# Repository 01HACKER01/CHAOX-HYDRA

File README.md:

# CHAOX-HYDRA

## What is this 
this is a diy flipper 0 which i tried to make it has 7 buttons and a screen it works on a esp32 mini.

## why it exists
i was quite amazed by the flipper 0 like how it can change the traffic lights and steal any rfid connections so i was amazed by its powers so i thought lets try to make this i thought i will watch like how it works but studying is quite boring.

## how to assemble
the pcb is connected to the case using glue or double sided tape adn teh case is connected together using brass inserts adn screws.

## Issues 
i dont think it has some issues but if u think it has some issues please let me know ill try to fix them right away.

## BOM

| Component | Qty | Est. Unit Price | Estimated Total | Purchase Link |
|---|---:|---:|---:|---|
| Seeed XIAO ESP32-C5 | 1 | $7–12 | $7–12 | [Alibaba](https://www.alibaba.com/trade/search?SearchText=Seeed+XIAO+ESP32-C5) |
| MCP23017 I/O Expander | 1 | $1–3 | $1–3 | [Alibaba](https://www.alibaba.com/trade/search?SearchText=MCP23017+module) |
| LIS3DH Accelerometer | 1 | $2–5 | $2–5 | [Alibaba](https://www.alibaba.com/trade/search?SearchText=LIS3DH+accelerometer+module) |
| SPI TFT Display | 1 | $4–10 | $4–10 | [Alibaba](https://www.alibaba.com/trade/search?SearchText=2.4+inch+SPI+TFT+240x320) |
| MicroSD Socket / Module | 1 | $1–3 | $1–3 | [Alibaba](https://www.alibaba.com/trade/search?SearchText=microSD+SPI+module) |
| CC1101 RF Module | 1 | $2–5 | $2–5 | [Alibaba](https://www.alibaba.com/trade/search?SearchText=CC1101+wireless+module) |
| PN532 NFC Module | 1 | $2–5 | $2–5 | [Alibaba](https://www.alibaba.com/trade/search?SearchText=PN532+NFC+module) |
| IR Receiver | 1 | $0.20–1 | $0.20–1 | [Alibaba](https://www.alibaba.com/trade/search?SearchText=infrared+receiver+38kHz) |
| IR Transmitter LED | 1 | $0.10–0.50 | $0.10–0.50 | [Alibaba](https://www.alibaba.com/trade/search?SearchText=infrared+transmitter+LED) |
| Buzzer | 1 | $0.20–1 | $0.20–1 | [Alibaba](https://www.alibaba.com/trade/search?SearchText=3.3V+active+buzzer) |
| Tactile Buttons | 7 | $0.05–0.20 | $0.35–1.40 | [Alibaba](https://www.alibaba.com/trade/search?SearchText=tactile+push+button+switch) |
| Status LED | 1 | $0.05–0.20 | $0.05–0.20 | [Alibaba](https://www.alibaba.com/trade/search?SearchText=0603+LED) |
| Rechargeable Battery | 1 | $3–7 | $3–7 | [Alibaba](https://www.alibaba.com/trade/search?SearchText=3.7V+rechargeable+LiPo+battery) |
| Battery Charger | 1 | $1–3 | $1–3 | [Alibaba](https://www.alibaba.com/trade/search?SearchText=LiPo+battery+charger+module) |
| Voltage Regulator | 1 | $0.50–2 | $0.50–2 | [Alibaba](https://www.alibaba.com/trade/search?SearchText=voltage+regulator+module) |
| Power Switch | 1 | $0.20–1 | $0.20–1 | [Alibaba](https://www.alibaba.com/trade/search?SearchText=miniature+maintained+power+switch) |
| Passive Components & Connectors | 1 lot | $2–5 | $2–5 | [Alibaba](https://www.alibaba.com/trade/search?SearchText=SMD+resistor+capacitor+connector+kit) |
| Custom PCB | 1 | $10 | $10 | |
| Enclosure & Mounting Hardware | 1 set | $10 | $10 ||

| Category | Estimated Cost |
|---|---:|
| Electronics and modules | $24–60 |
| PCB and enclosure | $8–25 |
| **Estimated overall total** | **$32–100** |

## The END
that was it thank you very much

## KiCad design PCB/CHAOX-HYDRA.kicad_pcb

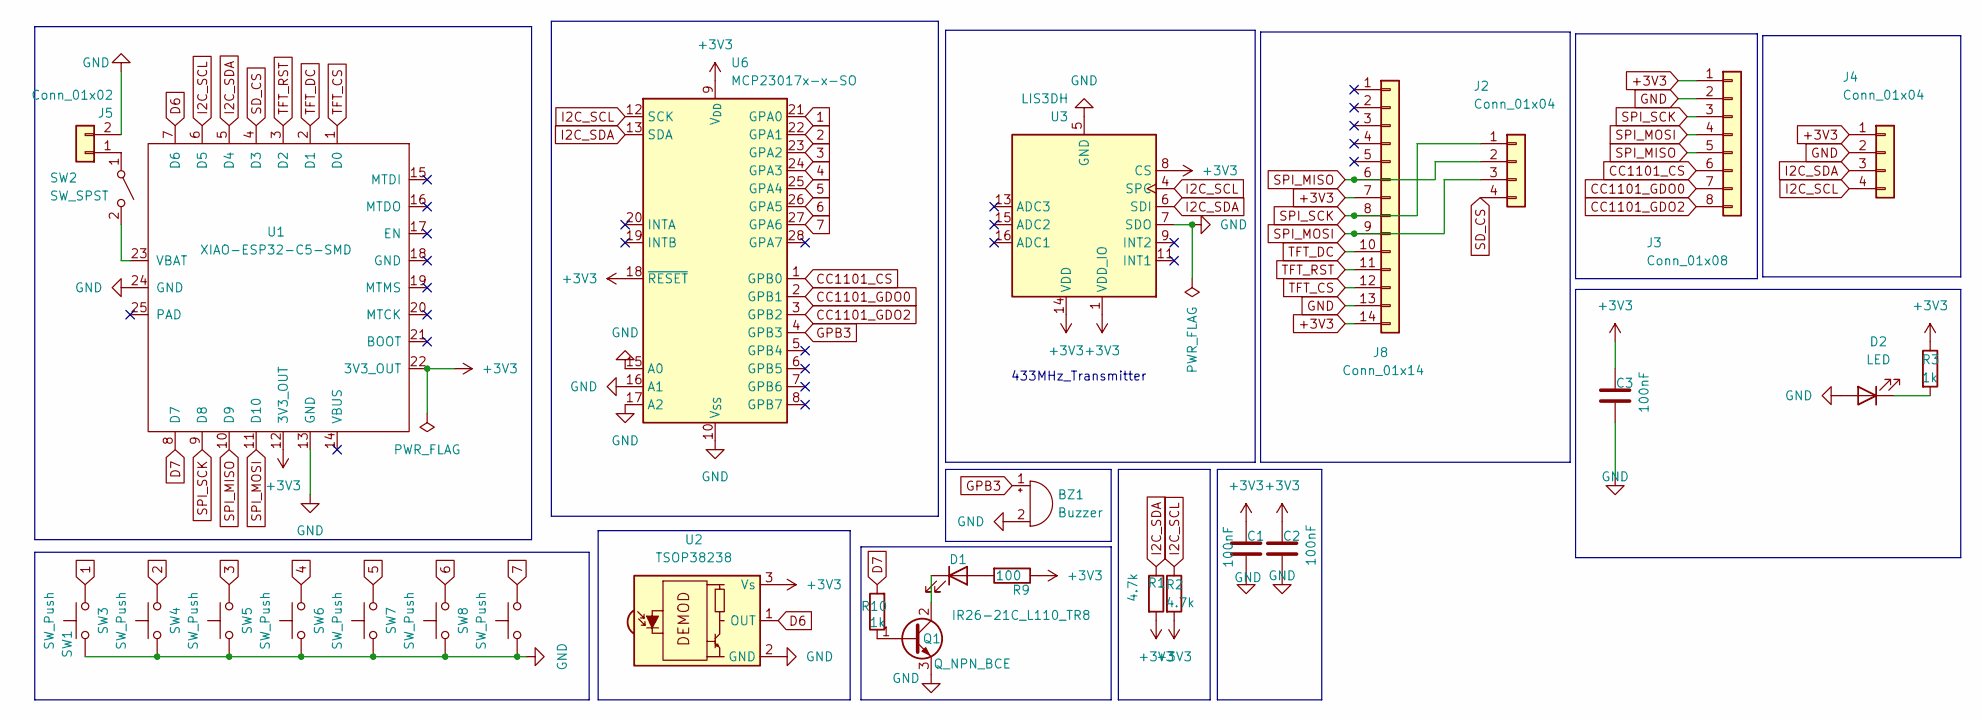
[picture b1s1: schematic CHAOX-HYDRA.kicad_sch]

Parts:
BZ1: Buzzer; Buzzer_12x9.5RM7.6
C1, C2, C3: 100nF; C_0805_2012Metric
D1: IR26-21C_L110_TR8; LED_1206_3216Metric
D2: LED; LED_0805_2012Metric
J2, J4: Conn_01x04; PinHeader_1x04_P2.54mm_Vertical
J3: Conn_01x08; PinHeader_1x08_P2.54mm_Vertical
J5: Conn_01x02; PinHeader_1x02_P2.54mm_Vertical
J8: Conn_01x14; PinHeader_1x14_P2.54mm_Vertical
Q1: Q_NPN_BCE; TO-92_Inline
R1, R2: 4.7k; R_0805_2012Metric
R3, R10: 1k; R_0805_2012Metric
R9: 100; R_0805_2012Metric
SW1, SW3, SW4, SW5, SW6, SW7, SW8: SW_Push; SW_PUSH_6mm
SW2: SW_SPST; SW_PUSH_6mm
U1: XIAO-ESP32-C5-SMD
U2: TSOP38238; Vishay_MINICAST-3Pin
U3: LIS3DH; LGA-16_3x3mm_P0.5mm_LayoutBorder3x5y
U6: MCP23017x-x-SO; SOIC-28W_7.5x17.9mm_P1.27mm

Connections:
1: SW1.2, U6.21 (GPA0)
2: SW3.2, U6.22 (GPA1)
3: SW4.2, U6.23 (GPA2)
4: SW5.2, U6.24 (GPA3)
5: SW6.2, U6.25 (GPA4)
6: SW7.2, U6.26 (GPA5)
7: SW8.2, U6.27 (GPA6)
+3V3: C1.1, C2.1, C3.1, J3.1, J4.1, J8.7, J8.14, R1.2, R2.2, R3.1, R9.1, U1.12 (3V3_OUT), U1.22 (3V3_OUT), U2.3 (Vs), U3.1 (VDD_IO), U3.8 (CS), U3.14 (VDD), U6.9 (V_{DD}), U6.18 (~RESET)
CC1101_CS: J3.6, U6.1 (GPB0)
CC1101_GDO0: J3.7, U6.2 (GPB1)
CC1101_GDO2: J3.8, U6.3 (GPB2)
D6: U1.7 (D6), U2.1 (OUT)
D7: R10.2, U1.8 (D7)
GND: BZ1.2 (-), C1.2, C2.2, C3.2, D2.2 (A), J3.2, J4.2, J5.2, J8.13, Q1.3 (E), SW1.1, SW3.1, SW4.1, SW5.1, SW6.1, SW7.1, SW8.1, U1.13 (GND), U1.24 (GND), U2.2 (GND), U3.5 (GND), U3.7 (SDO), U3.10 (GND), U3.12 (GND), U6.10 (V_{SS}), U6.15 (A0), U6.16 (A1), U6.17 (A2)
GPB3: BZ1.1 (+), U6.4 (GPB3)
I2C_SCL: J4.4, R2.1, U1.6 (D5), U3.4 (SPC), U6.12 (SCK)
I2C_SDA: J4.3, R1.1, U1.5 (D4), U3.6 (SDI), U6.13 (SDA)
unnamed: D1.2 (A), R9.2
unnamed: D1.1 (K), Q1.2 (C)
unnamed: D2.1 (K), R3.2
unnamed: J5.1, SW2.1 (A)
unnamed: Q1.1 (B), R10.1
unnamed: SW2.2 (B), U1.23 (VBAT)
SD_CS: J2.4, U1.4 (D3)
SPI_MISO: J2.2, J3.5, J8.6, U1.10 (D9)
SPI_MOSI: J2.3, J3.4, J8.9, U1.11 (D10)
SPI_SCK: J2.1, J3.3, J8.8, U1.9 (D8)
TFT_CS: J8.12, U1.1 (D0)
TFT_DC: J8.10, U1.2 (D1)
TFT_RST: J8.11, U1.3 (D2)

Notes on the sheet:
433MHz_Transmitter

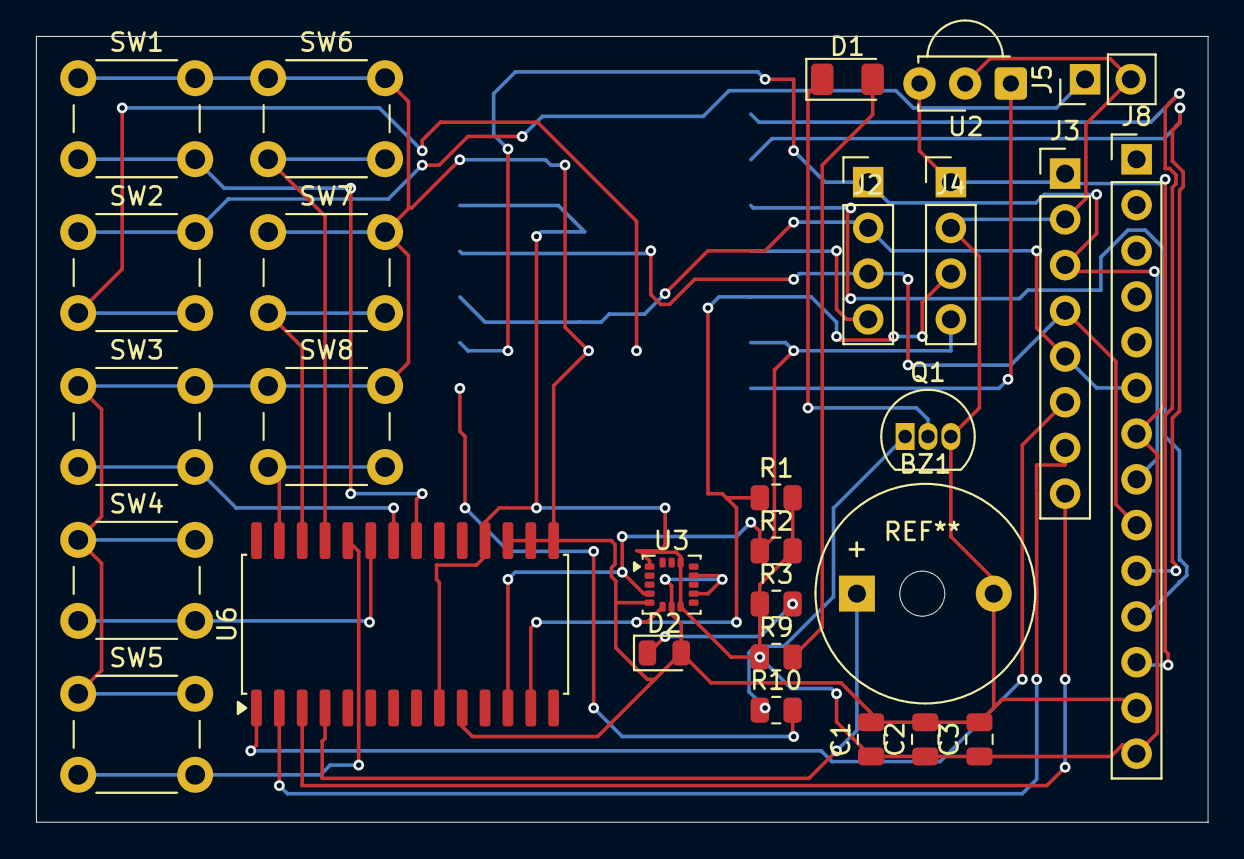
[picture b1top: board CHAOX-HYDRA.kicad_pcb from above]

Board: 2 copper layers, 65.1 x 43.7 mm, 29 parts (1 on the bottom side), 30 nets.

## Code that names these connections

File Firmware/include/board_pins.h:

#pragma once
#include <Arduino.h>

namespace Pins {
  constexpr int TFT_CS = 1;
  constexpr int TFT_DC = 0;
  constexpr int TFT_RST = 25;
  constexpr int SD_CS = 7;

  constexpr int I2C_SDA = 23;
  constexpr int I2C_SCL = 24;

  constexpr int IR_RX = 11;
  constexpr int IR_TX = 12;

  constexpr int SPI_SCK = 8;
  constexpr int SPI_MISO = 9;
  constexpr int SPI_MOSI = 10;

  constexpr uint8_t MCP23017_ADDR = 0x20;
  constexpr uint8_t LIS3DH_ADDR = 0x18;

  constexpr uint8_t RADIO_CS = 0;
  constexpr uint8_t RADIO_GDO0 = 1;
  constexpr uint8_t RADIO_GDO2 = 2;
  constexpr uint8_t BUZZER = 3;

  constexpr uint8_t BUTTON_FIRST = 8;
  constexpr uint8_t BUTTON_COUNT = 7;
}
